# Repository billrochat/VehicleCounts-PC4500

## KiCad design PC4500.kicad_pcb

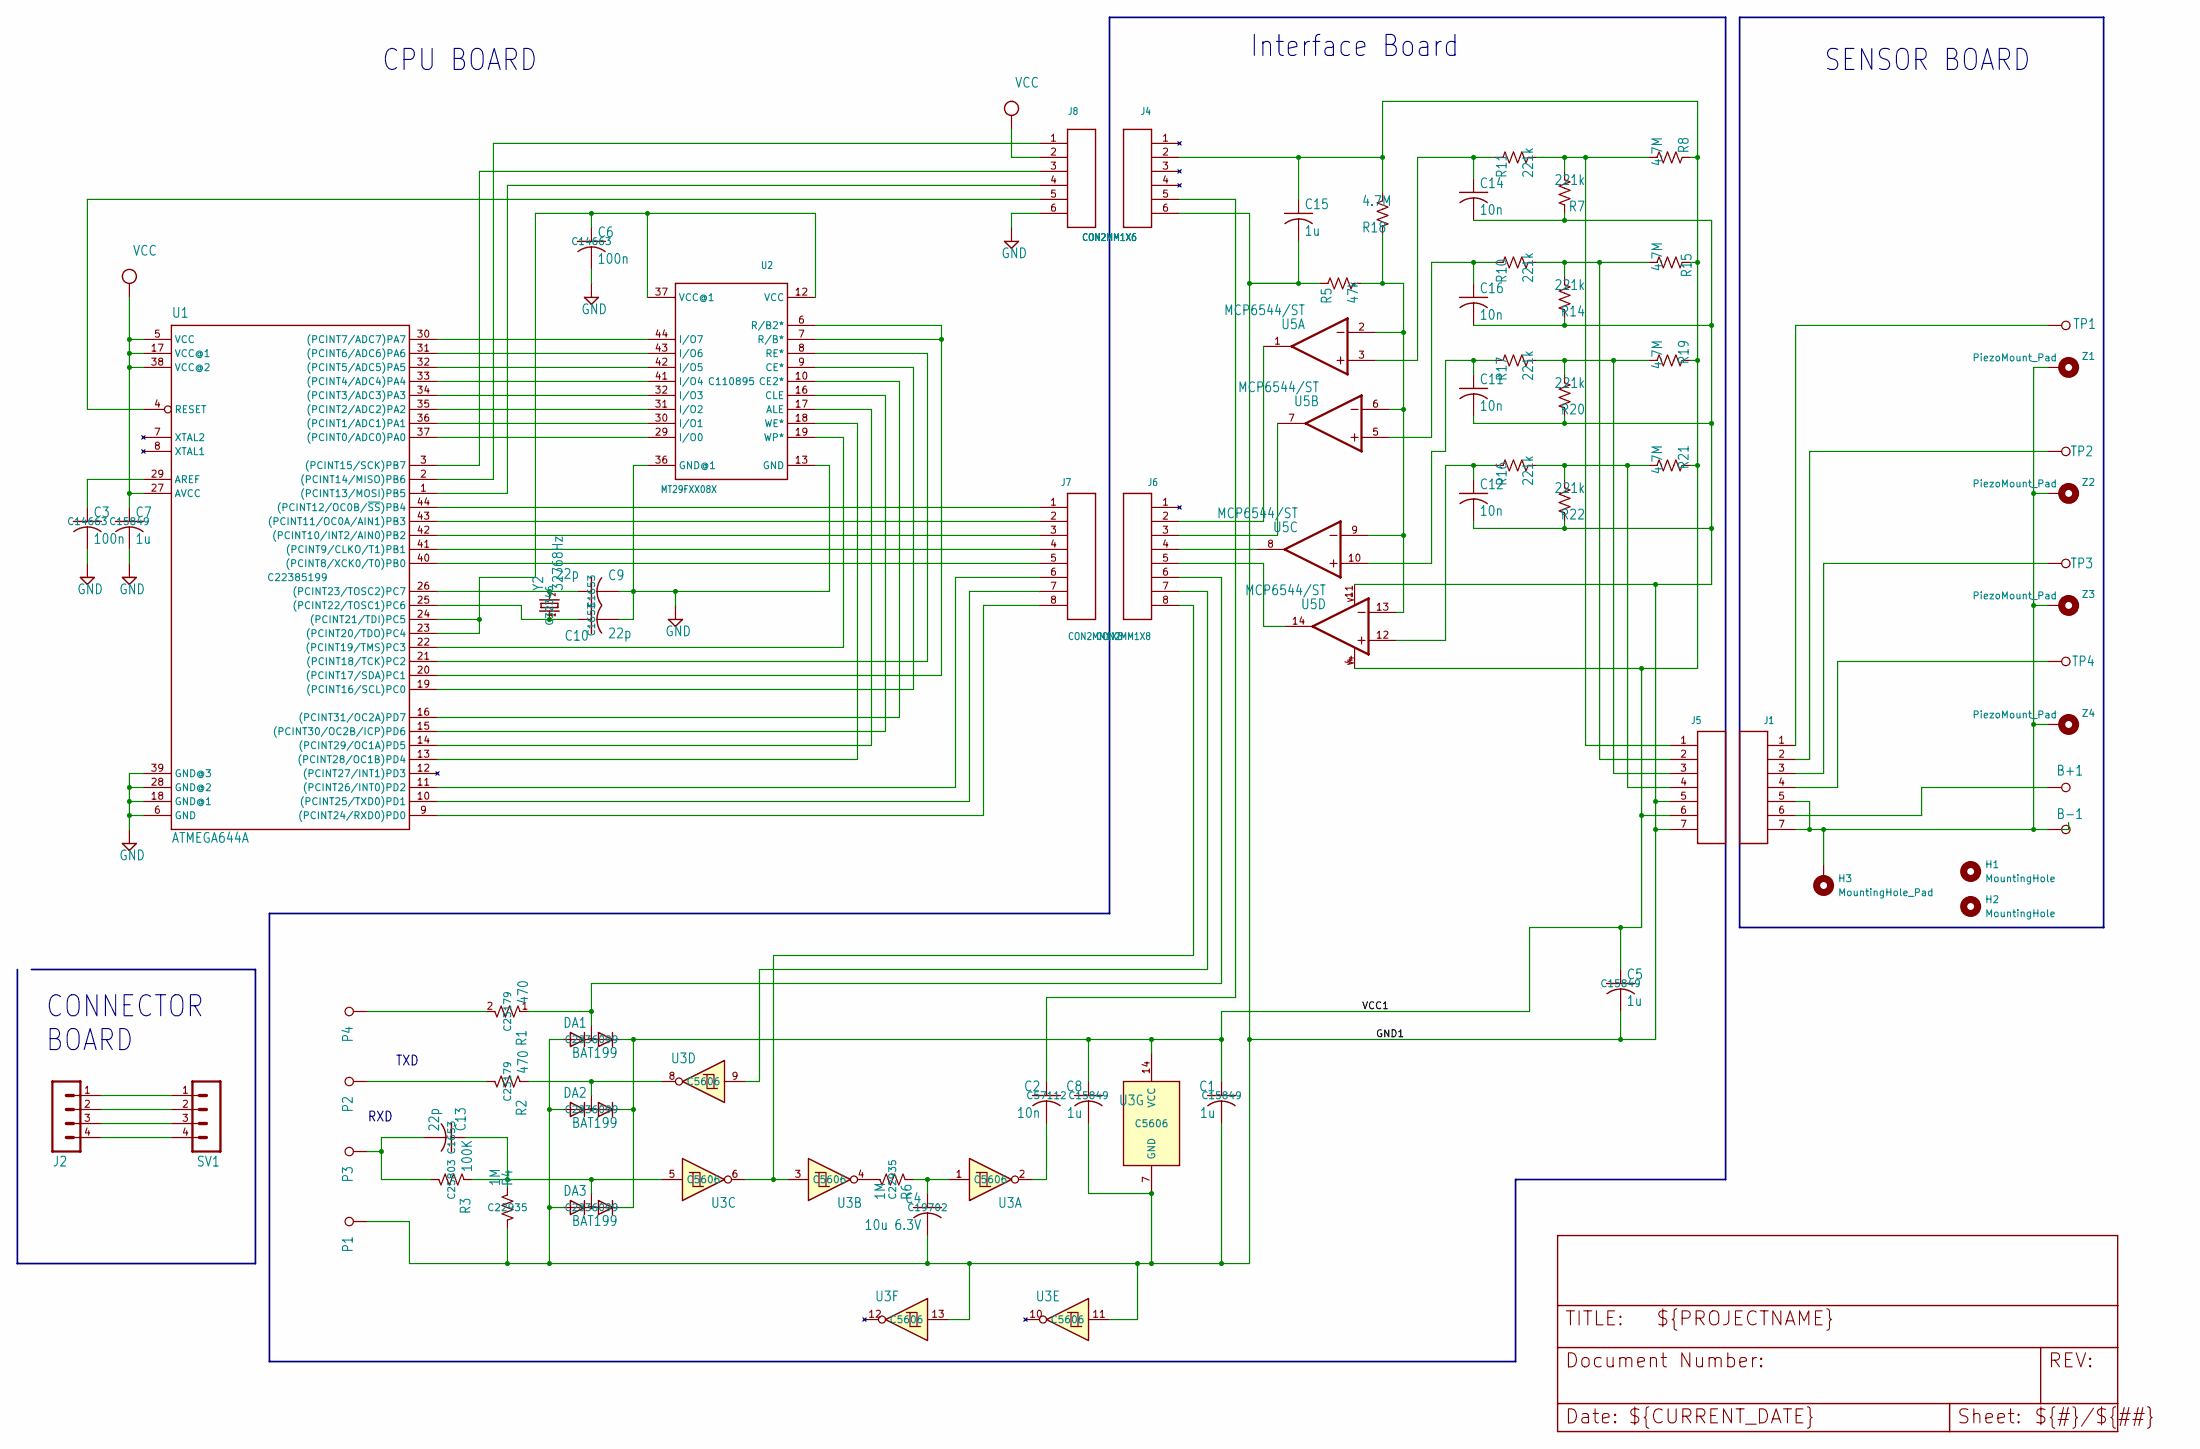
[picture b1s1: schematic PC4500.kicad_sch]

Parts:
B+1: LSP10; TestPoint_THTPad_D2.0mm_Drill1.0mm
B-1: LSP10; TestPoint_THTPad_D2.0mm_Drill1.0mm
C1, C5, C7, C8, C15: 1u; C_0603_1608Metric; MPN C15849
C2, C11, C12, C14, C16: 10n; C_0603_1608Metric; MPN C57112
C3, C6: 100n; C_0603_1608Metric; MPN C14663
C4: 10u 6.3V; C_0603_1608Metric; MPN C19702
C9, C10, C13: 22p; C_0603_1608Metric; MPN C1653
DA1, DA2, DA3: BAT199; SOT-23; MPN C2836099
H1, H2: MountingHole; MountingHole_3.2mm_M3
H3: MountingHole_Pad; MountingHole_0.254in-Pad_0.125in-Hole_THT_TopBottom
J1: CON2MM1X7FHSMD; PinSocket_1x07_P2.00mm_Vertical_SMD_Pin1Right
J2: CONXALL4PCBEDGE; CON4PCB-EDGE
J4, J8: CON2MM1X6; PinHeader_1x06_P2.00mm_Vertical
J5: CON2MM1X7; PinHeader_1x07_P2.00mm_Vertical
J6, J7: CON2MM1X8; PinHeader_1x08_P2.00mm_Vertical
P1, P2, P3, P4: .1IN-SC-PAD; TestPoint_Pad_1.5x1.5mm
R1, R2: 470; R_0603_1608Metric; MPN C23179
R3: 100K; R_0603_1608Metric; MPN C25803
R4, R6: 1M; R_0603_1608Metric; MPN C22935
R5: 47k; R_0603_1608Metric; MPN C25819
R7, R10, R11, R14, R16, R17, R20, R22: 221k; R_0603_1608Metric; MPN C23341
R8, R15, R18, R19, R21: 4.7M; R_0603_1608Metric; MPN C23163
SV1: MA04-1; PinHeader_1x04_P2.54mm_Vertical
TP1, TP2, TP3, TP4: TPSQTP16SQ; TestPoint_Pad_1.5x1.5mm
U1: ATMEGA644A; TQFP-44_10x10mm_P0.8mm; MPN C22385199
U2: MT29FXX08X; TSOP-I-48_18.4x12mm_P0.5mm; MPN C110895
U3: 74HC14; TSSOP-14_4.4x5mm_P0.65mm; MPN C5606
U5: MCP6544/ST; TSSOP-14_4.4x5mm_P0.65mm; MPN C3658291; DIGIKEY MCP6544-I/ST-ND
Y2: 32768Hz; Crystal_SMD_MicroCrystal_CC5V-T1A-2Pin_4.1x1.5mm; MPN C32346
Z1, Z2, Z3, Z4: PiezoMount_Pad; PiezoMount_0.48in-Pad_.406in-Hole__TopBottom

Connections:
/GND1: C1.2, C4.2, C5.2, C8.2, C11.2, C12.2, C14.2, C15.2, C16.2, DA1.1 (A), DA2.1 (A), DA3.1 (A), J4.6, J5.5, J5.7, P1.1, R4.1, R5.1, R7.1, R14.1, R20.1, R22.1, U3.7 (GND), U3.11, U3.13, U5.11 (V-)
/VCC1: C1.1, C5.1, C8.1, C15.1, DA1.2 (C), DA2.2 (C), DA3.2 (C), J4.2, J5.6, R8.1, R15.1, R18.2, R19.1, R21.1, U3.14 (VCC), U5.4 (V+)
GND: C3.2, C6.2, C7.2, C9.2, C10.2, J8.6, U1.6 (GND), U1.18 (GND@1), U1.28 (GND@2), U1.39 (GND@3), U2.13 (GND), U2.36 (GND@1)
unnamed: B+1.1, J1.6
unnamed: B-1.1, H3.1, J1.5, J1.7, Z1.1, Z2.1, Z3.1, Z4.1
unnamed: C2.1, J4.5
unnamed: C2.2, U3.2
unnamed: C4.1, R6.1, U3.1
unnamed: C13.2, P3.1, R3.2
unnamed: DA1.3 (AC), J6.6, R1.1
unnamed: DA2.3 (AC), R2.1, U3.8
unnamed: C13.1, DA3.3 (AC), R3.1, R4.2, U3.5
unnamed: J1.1, TP1.1
unnamed: J1.2, TP2.1
unnamed: J1.3, TP3.1
unnamed: J1.4, TP4.1
unnamed: J2.1, SV1.1
unnamed: J2.2, SV1.2
unnamed: J2.3, SV1.3
unnamed: J2.4, SV1.4
unnamed: J5.1, R7.2, R8.2, R11.2
unnamed: J5.2, R10.2, R14.2, R15.2
unnamed: J5.3, R17.2, R19.2, R20.2
unnamed: J5.4, R16.2, R21.2, R22.2
unnamed: J6.2, U5.1 (OUT)
unnamed: J6.3, U5.7 (OUT)
unnamed: J6.4, U5.8 (OUT)
unnamed: J6.5, U5.14 (OUT)
unnamed: J6.7, U3.9
unnamed: J6.8, U3.3, U3.6
unnamed: J7.1, U1.44 ((PCINT12/OC0B/~SS)PB4)
unnamed: J7.2, U1.43 ((PCINT11/OC0A/AIN1)PB3)
unnamed: J7.3, U1.42 ((PCINT10/INT2/AIN0)PB2)
unnamed: J7.4, U1.41 ((PCINT9/CLKO/T1)PB1)
unnamed: J7.5, U1.40 ((PCINT8/XCK0/T0)PB0)
unnamed: J7.6, U1.11 ((PCINT26/INT0)PD2)
unnamed: J7.7, U1.10 ((PCINT25/TXD0)PD1)
unnamed: J7.8, U1.9 ((PCINT24/RXD0)PD0)
unnamed: P2.1, R2.2
unnamed: P4.1, R1.2
unnamed: R6.2, U3.4
unnamed: U1.37 ((PCINT0/ADC0)PA0), U2.29 (I/O0)
unnamed: U1.36 ((PCINT1/ADC1)PA1), U2.30 (I/O1)
unnamed: U1.35 ((PCINT2/ADC2)PA2), U2.31 (I/O2)
unnamed: U1.34 ((PCINT3/ADC3)PA3), U2.32 (I/O3)
unnamed: U1.33 ((PCINT4/ADC4)PA4), U2.41 (I/O4)
unnamed: U1.32 ((PCINT5/ADC5)PA5), U2.42 (I/O5)
unnamed: U1.31 ((PCINT6/ADC6)PA6), U2.43 (I/O6)
unnamed: U1.30 ((PCINT7/ADC7)PA7), U2.44 (I/O7)
unnamed: J8.4, U1.1 ((PCINT13/MOSI)PB5)
unnamed: J8.1, U1.2 ((PCINT14/MISO)PB6)
unnamed: J8.3, U1.3 ((PCINT15/SCK)PB7)
unnamed: U1.19 ((PCINT16/SCL)PC0), U2.9 (CE*)
unnamed: U1.20 ((PCINT17/SDA)PC1), U2.6 (R/B2*), U2.7 (R/B*)
unnamed: U1.21 ((PCINT18/TCK)PC2), U2.8 (RE*)
unnamed: U1.22 ((PCINT19/TMS)PC3), U2.19 (WP*)
unnamed: C6.1, U1.23 ((PCINT20/TDO)PC4), U1.24 ((PCINT21/TDI)PC5), U2.12 (VCC), U2.37 (VCC@1)
unnamed: C10.1, U1.25 ((PCINT22/TOSC1)PC6), Y2.1
unnamed: C9.1, U1.26 ((PCINT23/TOSC2)PC7), Y2.2
unnamed: U1.13 ((PCINT28/OC1B)PD4), U2.18 (WE*)
unnamed: U1.14 ((PCINT29/OC1A)PD5), U2.17 (ALE)
unnamed: U1.15 ((PCINT30/OC2B/ICP)PD6), U2.16 (CLE)
unnamed: U1.16 ((PCINT31/OC2A)PD7), U2.10 (CE2*)
unnamed: C3.1, U1.29 (AREF)
unnamed: J8.5, U1.4 (RESET)
unnamed: C14.1, R11.1, U5.3 (+IN)
unnamed: R5.2, R18.1, U5.2 (-IN), U5.6 (-IN), U5.9 (-IN), U5.13 (-IN)
unnamed: C16.1, R10.1, U5.5 (+IN)
unnamed: C11.1, R17.1, U5.10 (+IN)
unnamed: C12.1, R16.1, U5.12 (+IN)
VCC: C7.1, J8.2, U1.5 (VCC), U1.17 (VCC@1), U1.27 (AVCC), U1.38 (VCC@2)

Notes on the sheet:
Interface Board
TXD
CPU BOARD
CONNECTOR BOARD
RXD
SENSOR BOARD

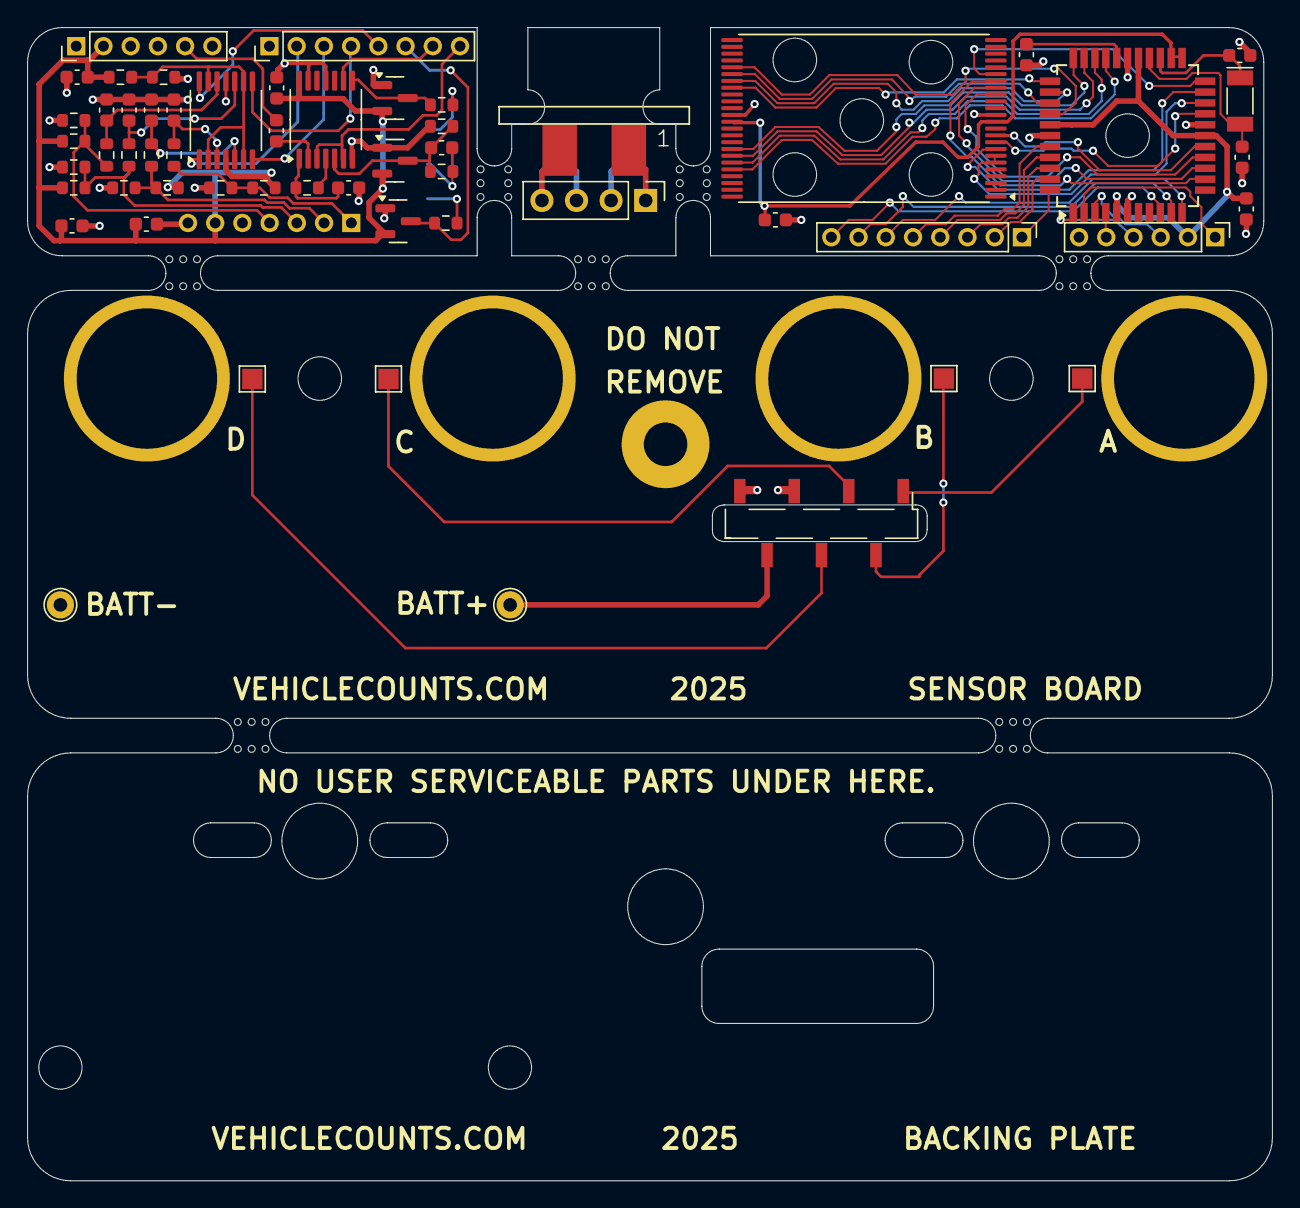
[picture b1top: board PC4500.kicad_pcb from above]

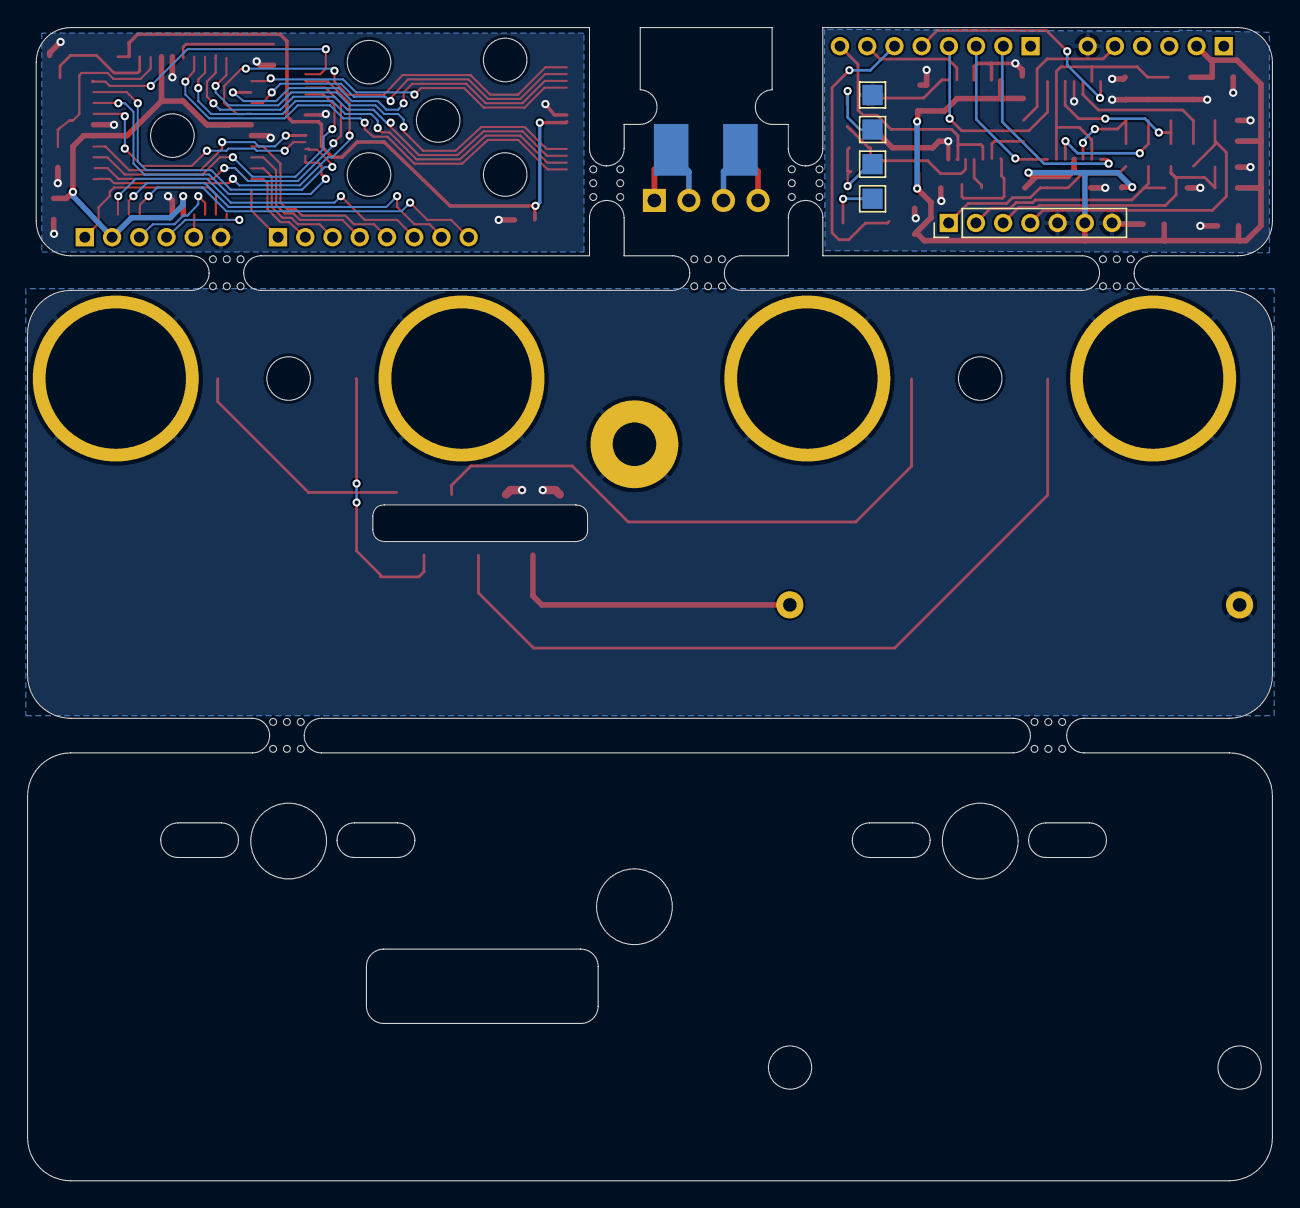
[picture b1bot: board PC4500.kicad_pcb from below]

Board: 2 copper layers, 91.4 x 84.7 mm, 121 parts (5 on the bottom side), 71 nets.

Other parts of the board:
@HOLE0, @HOLE1, @HOLE2, @HOLE3, @HOLE4, @HOLE5, @HOLE6, @HOLE7, @HOLE8, @HOLE9, @HOLE10, @HOLE11, @HOLE12, @HOLE13, @HOLE14, @HOLE15, @HOLE16, @HOLE17, @HOLE18, @HOLE19, @HOLE20, @HOLE21, @HOLE22, @HOLE23, @HOLE24, @HOLE25, @HOLE26, @HOLE27, @HOLE28, @HOLE29, @HOLE30, @HOLE31, @HOLE32, @HOLE33, @HOLE34, @HOLE35, @HOLE36, @HOLE37, @HOLE38, @HOLE39, @HOLE40, @HOLE41, @HOLE42, @HOLE43, @HOLE44, @HOLE45, @HOLE46, @HOLE47, @HOLE48, @HOLE49, @HOLE50, @HOLE53, @HOLE54: (no value)
